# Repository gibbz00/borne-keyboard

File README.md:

# Borne V1 Keyboard

V2 interest check is now live: https://www.reddit.com/r/mechmarket/comments/10xzn65/ic_borne_v2_a_slim_wireless_and_split_keyboard/

Source files for the Borne Keyboard; a wireless, split, 36-key, orthogonal keyboard with a comparatively large battery capacity that should last over two months.
Also of low profile at a max height of about 17 mm (0.67 in).
Ready-made ZMK and Adafruit nrf52 bootloader binaries are placed in the `firmware/builds` directory.

Currently rocking this keyboard layout: http://www.keyboard-layout-editor.com/#/gists/0e81bf405ebbc268280f0506f7d0e771

**PLEASE NOTE THAT V1 IS A WORKING PROOF OF CONCEPT. Don't copy this project mindlessly and expect everything to work out of the box. I have notes containing over 500 points of improvements or cautions when working on this project, many of which to be added as repo issues in the near future.**

Kicad 6 and its component libraries are required to properly explore the majority of electronic design files. 

https://www.kicad.org/libraries/download/

Arch users simply install `kicad-library` and `kicad-library-3d-nightly` from the official repository.

# Customizing the keymap with ZMK

Necessary ZMK know-how can be found in its official documentation or in its welcoming community discord server: 

https://zmk.dev/docs

https://zmk.dev/community/discord/invite

## Building with GitHub Actions

Allows for keymap customizations to be done without going through the hassle of installing the respective toolchains. It works by automating firmware builds on a cloud server upon repository changes.

#### Repo setup (only once)
Log in/sign up to a personal GitHub account.
Fork https://github.com/gibbz00/borne-zmk-config
#### Keymap updates
Edit `config/borne.keymap`.
Commit and push changes to your personal repo.
#### Retrieving firmware images
In the browser; navigate to "Actions".
Select the latest workflow run.
A "firmware" artifact should appear if all went well, clicking on it should start a zip download, unzip it once completed.
#### Flashing the keyboard
Only the left shield/half/side needs to be built to update the keymap.
Connect the half over USB, put it in bootloader mode (double press reset), and make sure the device storage is mounted. 
Last step is to copy over the `borne_left-borne-zmk.uf2` file to the new USB storage device and wait until the blue LED stops blinking rapidly.

## Local builds and flashing

### Preparations

The following dependencies are required to build ZMK:
* zephyr-sdk 
* python-jsonschema
* remarshal

And for the Adafruit nRF52 bootloader:
* arm-none-eabi-gcc
* python-intelhex

For Arch Linux based distributions: All packages exist in the same name on AUR, e.g:
```
yay -S --needed python-intelhex arm-none-eabi-gcc zephyr-sdk python-jsonschema remarshal 
```

Bootloader and ZMK exist as submodules in this repository. (Not yet merged upstream.)
```
git clone URL && git submodule update
```

All firmware files unique to this keyboard are found in:
```
firmware/Adafruit_nRF52_Bootloader/src/boards/borne_keyboard/
firmware/zmk/app/boards/arm/borne-keyboard/
firmware/zmk/app/boards/shields/borne-keyboard/
```

Those only interested in updating the keymap need not look any further than:
```
firmware/zmk/app/boards/shields/borne-keyboard/borne.keymap
```

### Building ZMK

Only the left shield/half/side needs to be built to update the keymap:
```
# in the firmware/zmk/app directory
west build -d build/left --pristine --board borne -- -DSHIELD=borne_left
```
### Flashing ZMK
Connect the half over USB, put it in bootloader mode (double press reset), and make sure the device storage is mounted. Then:
```
# still in the firmware/zmk/app directory
cp build/left/zephyr/zmk.uf2 path_to_borne_mass_storage/CURRENT.uf2
```

If necessary, change the occurrences of "left" to "right" to build the other half. 

### Adafruit nrf52 bootloader

Multiple ways of building and then flashing the boards over UART is explained in Joric's diligent write-up: https://github.com/joric/nrfmicro/wiki/Bootloader

I only got flashing with OpenOCD on the Raspberry Pi 4 to work.
The hardware specific `openocd.cfg` is found in the `firmware` directory.
Additional resources on how to flash the nrf5240 with OpenOCD and a Raspberry Pi 4 are found at: https://www.rototron.info/circuitpython-nrf52840-dongle-openocd-pi-tutorial/

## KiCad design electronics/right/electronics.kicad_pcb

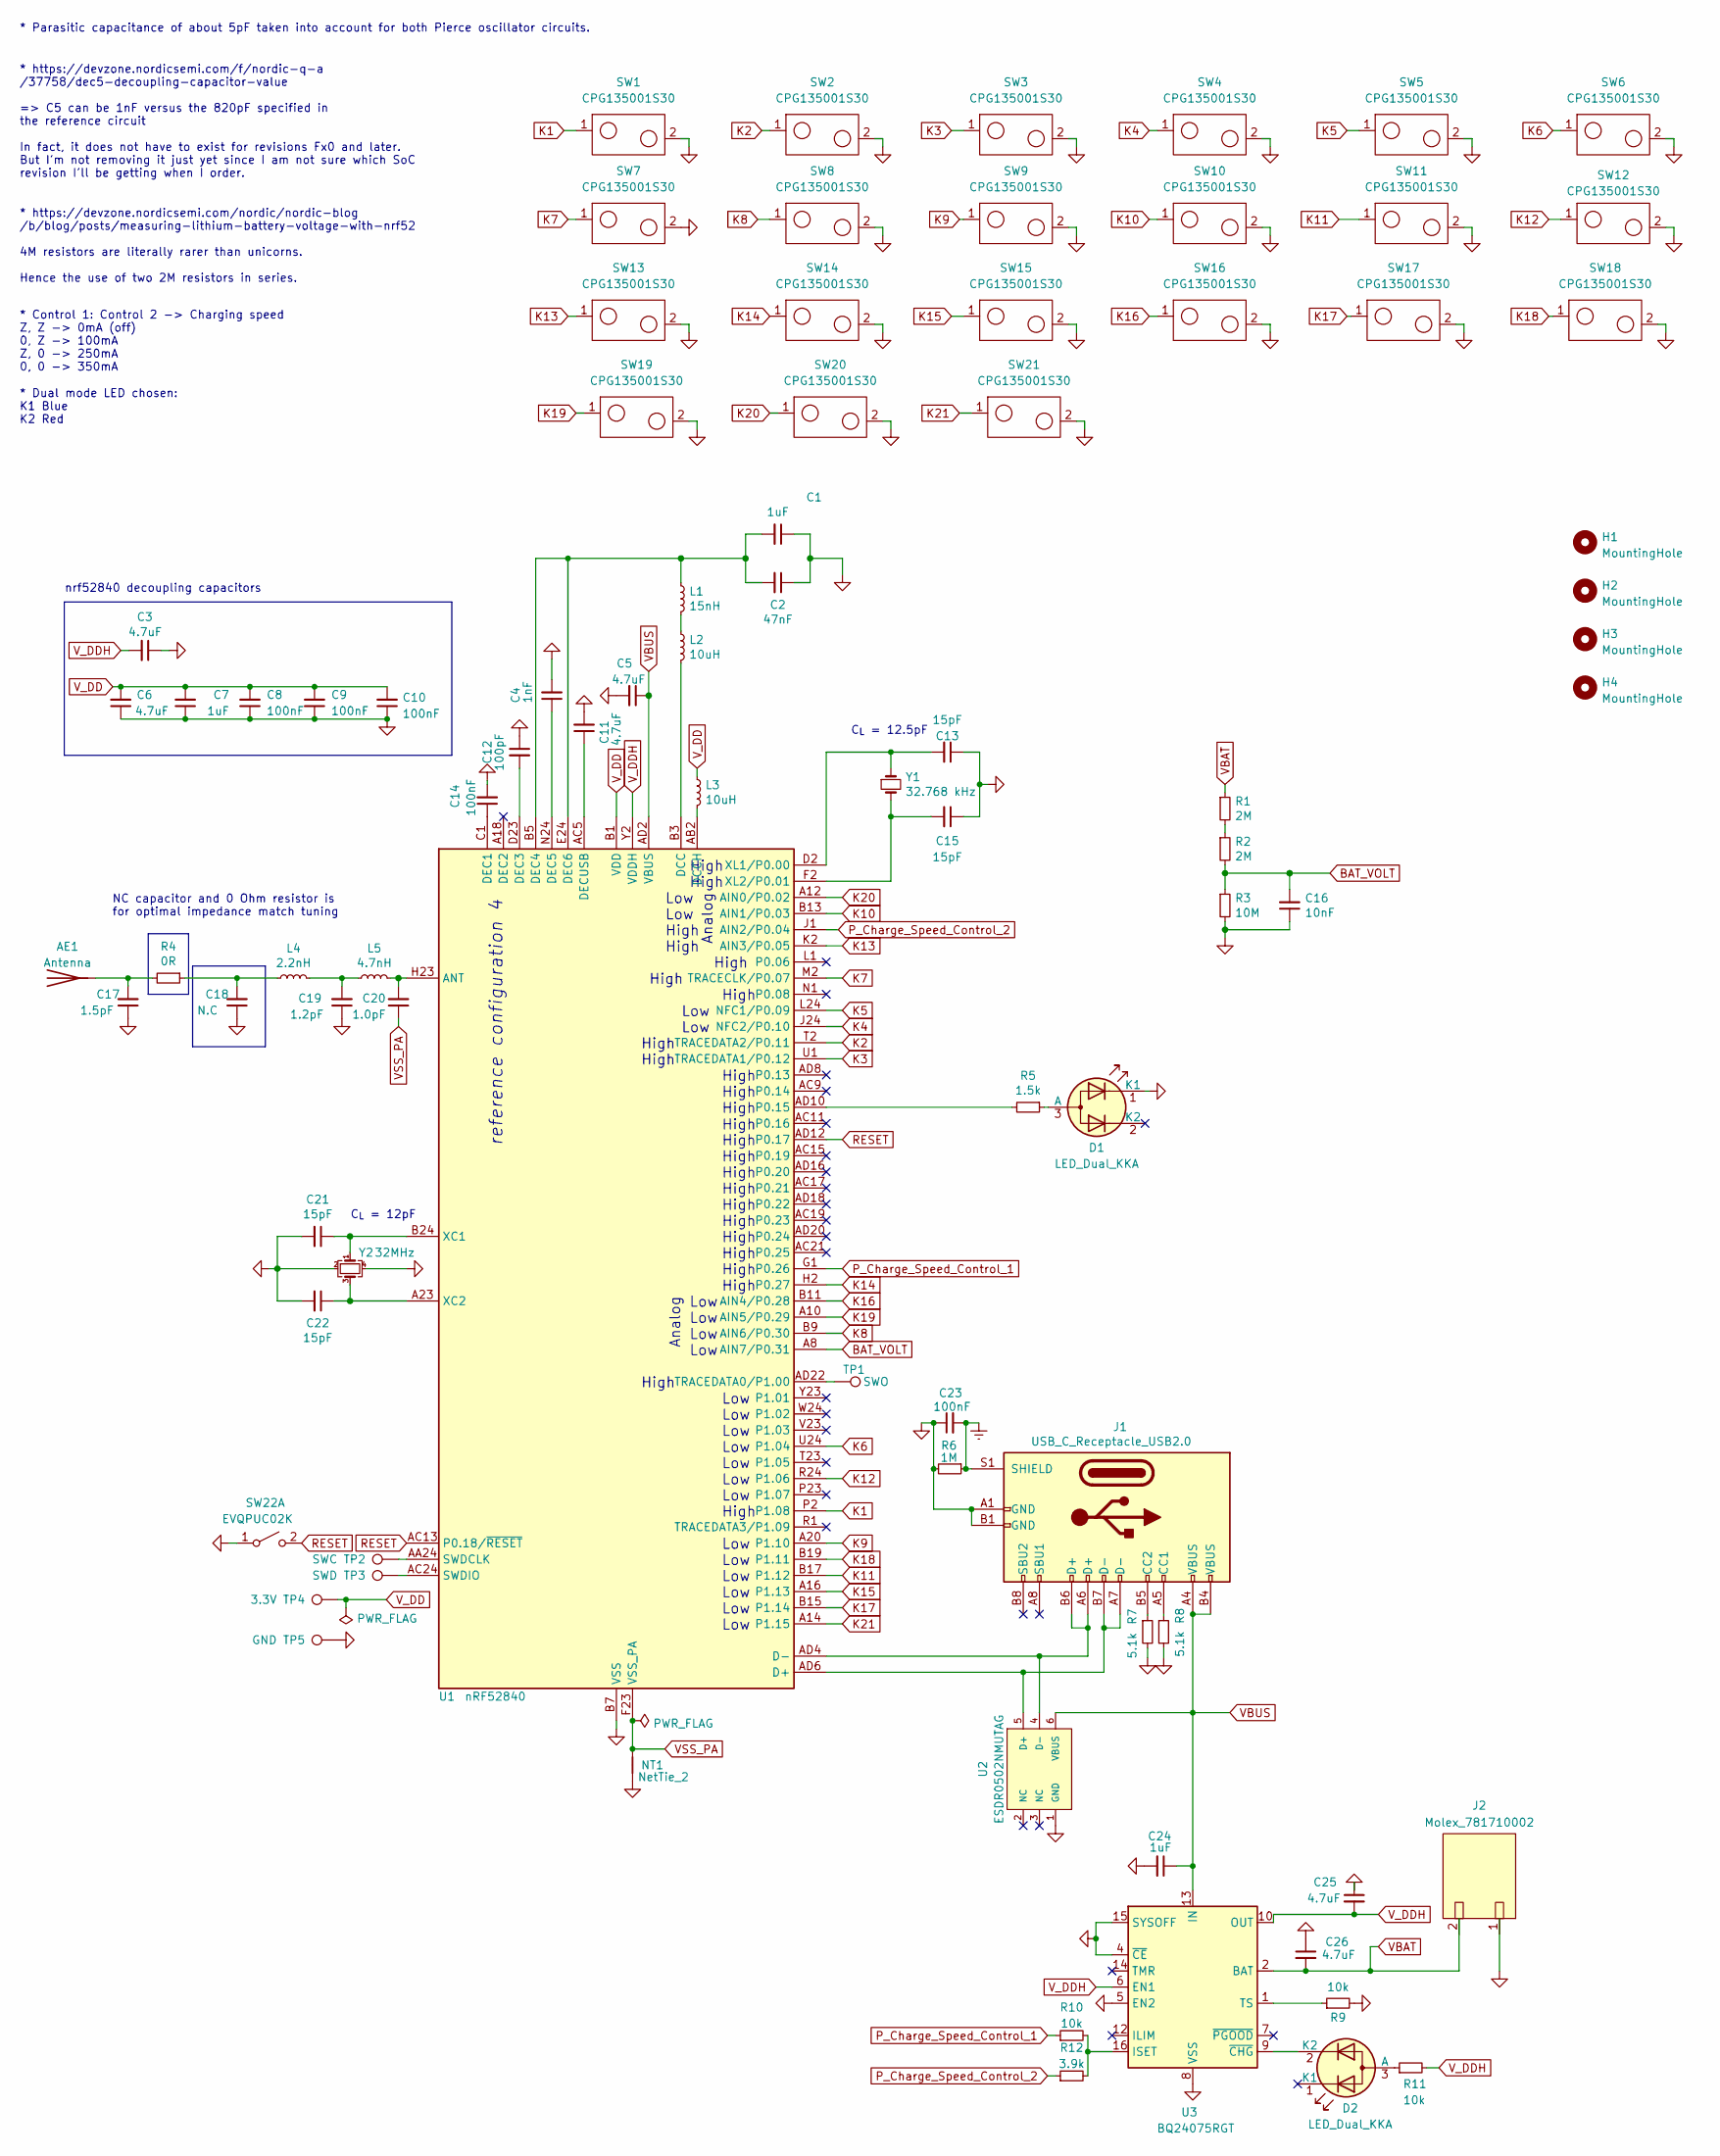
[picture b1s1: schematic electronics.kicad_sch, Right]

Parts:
AE1: Antenna; 2.4GHz-meander-antenna-right
C1, C7, C24: 1uF; C_0402_1005Metric; Manufacturer Part CL05A105KO5NNNC; LCSC Part C52923
C2: 47nF; C_0402_1005Metric; Manufacturer Part CL05B473KO5NNNC; LCSC Part C307434
C3, C5, C6, C11, C25, C26: 4.7uF; C_0402_1005Metric; Manufacturer Part CL05A475KP5NRNC; LCSC Part C368809
C4: 1nF; C_0402_1005Metric; Manufacturer Part CL05B104KA5NNNC; LCSC Part C1525
C8, C9, C10, C14: 100nF; C_0402_1005Metric; Manufacturer Part CL05B104KA5NNNC; LCSC Part C1525
C12: 100pF; C_0402_1005Metric; Manufacturer Part CL05C101JB5NNNC; LCSC Part C26409
C13, C15, C21, C22: 15pF; C_0402_1005Metric; Manufacturer Part CL05C150JB51PNC; LCSC Part C307341
C16: 10nF; C_0402_1005Metric; Manufacturer Part CL05B103KB5NNNC; LCSC Part C15195
C17: 1.5pF; C_0402_1005Metric; Manufacturer Part CL05C1R5CB5NNNC; LCSC Part C170150
C18: N.C; C_0402_1005Metric; Manufacturer Part CL05C010CB5NNNC; LCSC Part C371977
C19: 1.2pF; C_0402_1005Metric; Manufacturer Part CL05C010CB5NNNC; LCSC Part C371977
C20: 1.0pF; C_0402_1005Metric; Manufacturer Part CL05C010CB5NNNC; LCSC Part C371977
C23: 100nF; C_0402_1005Metric; Manufacturer Part CL05A475KP5NRNC; LCSC Part C368809
D1, D2: LED_Dual_KKA; LED-ARRAY-SMD_3P-L3.0-W2.0-L-FD; Manufacturer Part 12-22/BHR6C-A01/2C; LCSC Part C605447
H1, H2, H3, H4: MountingHole; screw-hole
J1: USB_C_Receptacle_USB2.0; USB-C-SMD_TYPE-C-31-M-13A-1; Manufacturer Part GT-USB-9014C; LCSC Part C2988367
J2: Molex_781710002; Molex_Pico-EZmate_78171-0002_1x02-1MP_P1.20mm_Vertical; Manufacturer Part 781710002; LCSC Part C505023
L1: 15nH; L_0402_1005Metric; Manufacturer Part MLG1005S15NJT000; LCSC Part C76763
L2, L3: 10uH; L_0603_1608Metric; Manufacturer Part MLF1608E100KTD00; LCSC Part C76732
L4: 2.2nH; L_0402_1005Metric; Manufacturer Part MLG1005S3N9BT000; LCSC Part C76775
L5: 4.7nH; L_0402_1005Metric; Manufacturer Part MLG1005S3N9BT000; LCSC Part C76775
NT1: NetTie_2; net-tie-2-tiny
R1, R2: 2M; R_0402_1005Metric; Manufacturer Part RC0402FR-072ML; LCSC Part C138014
R3: 10M; R_0402_1005Metric; Manufacturer Part RC0402FR-0710ML; LCSC Part C138067
R4: 0R; R_0402_1005Metric; Manufacturer Part RC0402FR-070RL; LCSC Part C106231
R5: 1.5k; R_0402_1005Metric; Manufacturer Part RC0402FR-071K5L; JLC Part C114759
R6: 1M; R_0402_1005Metric; Manufacturer Part RC0402FR-0710KL; LCSC Part C60490
R7, R8: 5.1k; R_0402_1005Metric; Manufacturer Part RC0402FR-0710KL; LCSC Part C60490
R9, R10, R11: 10k; R_0402_1005Metric; Manufacturer Part RC0402FR-0710KL; LCSC Part C60490
R12: 3.9k; R_0402_1005Metric; Manufacturer Part RC0402FR-073K9L; LCSC Part C131467
SW1, SW2, SW3, SW4, SW5, SW6, SW7, SW8, SW9, SW10, SW11, SW12, SW13, SW14, SW15, SW16, SW17, SW18, SW19, SW20, SW21: CPG135001S30; Kailh_socket_PG1350; Manufacturer Part CPG135001S30; JLC Part C5333465
SW22: EVQPUC02K; Panasonic_EVQPUL_EVQPUC; Manufacturer Part EVQPUC02K; JLC Part C79174
TP1: SWO; TestPoint_THTPad_1.5x1.5mm_Drill0.7mm
TP2: SWC; TestPoint_THTPad_1.5x1.5mm_Drill0.7mm
TP3: SWD; TestPoint_THTPad_1.5x1.5mm_Drill0.7mm
TP4: 3.3V; TestPoint_THTPad_1.5x1.5mm_Drill0.7mm
TP5: GND; TestPoint_THTPad_1.5x1.5mm_Drill0.7mm
U1: nRF52840; Nordic_AQFN-73-1EP_7x7mm_P0.5mm; Manufacturer Part NRF52840-QIAA-R; LCSC Part C1851953
U2: ESDR0502NMUTAG; Manufacturer Part ESDR0502NMUTBG; LCSC Part C327480
U3: BQ24075RGT; VQFN-16-1EP_3x3mm_P0.5mm_EP1.6x1.6mm; Manufacturer Part BQ24075RGTR; JLC Part C15464
Y1: 32.768 kHz; Crystal_SMD_2012-2Pin_2.0x1.2mm; Manufacturer Part SC20S-12.5PF20PPM; LCSC Part C97607
Y2: 32MHz; Crystal_SMD_2016-4Pin_2.0x1.6mm; Manufacturer Part Q22FA1280001800; LCSC Part C255896

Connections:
BAT_VOLT: C16.2, R2.2, R3.1, U1.A8 (AIN7/P0.31)
K1: SW1.1, U1.P2 (P1.08)
K2: SW2.1, U1.T2 (TRACEDATA2/P0.11)
K3: SW3.1, U1.U1 (TRACEDATA1/P0.12)
K4: SW4.1, U1.J24 (NFC2/P0.10)
K5: SW5.1, U1.L24 (NFC1/P0.09)
K6: SW6.1, U1.U24 (P1.04)
K7: SW7.1, U1.M2 (TRACECLK/P0.07)
K8: SW8.1, U1.B9 (AIN6/P0.30)
K9: SW9.1, U1.A20 (P1.10)
K10: SW10.1, U1.B13 (AIN1/P0.03)
K11: SW11.1, U1.B17 (P1.12)
K12: SW12.1, U1.R24 (P1.06)
K13: SW13.1, U1.K2 (AIN3/P0.05)
K14: SW14.1, U1.H2 (P0.27)
K15: SW15.1, U1.A16 (P1.13)
K16: SW16.1, U1.B11 (AIN4/P0.28)
K17: SW17.1, U1.B15 (P1.14)
K18: SW18.1, U1.B19 (P1.11)
K19: SW19.1, U1.A10 (AIN5/P0.29)
K20: SW20.1, U1.A12 (AIN0/P0.02)
K21: SW21.1, U1.A14 (P1.15)
unnamed: AE1.1 (A), C17.2, R4.2
unnamed: C18.2, L4.2, R4.1
unnamed: C19.2, L4.1, L5.1
unnamed: D1.3 (A), R5.1
unnamed: D2.3 (A), R11.1
unnamed: D2.2 (K2), U3.9 (~CHG)
unnamed: J1.A5 (CC1), R8.1
unnamed: J1.B5 (CC2), R7.1
unnamed: L1.2, L2.1
unnamed: R1.2, R2.1
unnamed: C20.2, L5.2, U1.H23 (ANT)
unnamed: J1.A7 (D-), J1.B7 (D-), U1.AD6 (D+), U2.5 (D+)
unnamed: J1.A6 (D+), J1.B6 (D+), U1.AD4 (D-), U2.4 (D-)
unnamed: L2.2, U1.B3 (DCC)
unnamed: L3.2, U1.AB2 (DCCH)
unnamed: C14.1, U1.C1 (DEC1)
unnamed: C12.2, U1.D23 (DEC3)
unnamed: C1.2, C2.2, L1.1, U1.B5 (DEC4), U1.E24 (DEC6)
unnamed: C4.1, U1.N24 (DEC5)
unnamed: C11.1, U1.AC5 (DECUSB)
unnamed: R5.2, U1.AD10 (P0.15)
unnamed: TP2.1, U1.AA24 (SWDCLK)
unnamed: TP3.1, U1.AC24 (SWDIO)
unnamed: TP1.1, U1.AD22 (TRACEDATA0/P1.00)
unnamed: C21.1, U1.B24 (XC1), Y2.1
unnamed: C22.1, U1.A23 (XC2), Y2.3
unnamed: C13.2, U1.D2 (XL1/P0.00), Y1.1
unnamed: C15.2, U1.F2 (XL2/P0.01), Y1.2
unnamed: R10.2, R12.2, U3.16 (ISET)
unnamed: R9.1, U3.1 (TS)
P_Charge_Speed_Control_1: R10.1, U1.G1 (P0.26)
P_Charge_Speed_Control_2: R12.1, U1.J1 (AIN2/P0.04)
RESET: SW22.2 (B), U1.AC13 (P0.18/~RESET), U1.AD12 (P0.17)
VBAT: C26.2, J2.2, R1.1, U3.2 (BAT), U3.3 (BAT)
VBUS: C5.1, C24.1, J1.A4 (VBUS), J1.B4 (VBUS), U1.AD2 (VBUS), U2.6 (VBUS), U3.13 (IN)
VSS_PA: C20.1, NT1.1, U1.F23 (VSS_PA)
V_DD: C6.2, C7.2, C8.2, C9.2, C10.2, L3.1, TP4.1, U1.A22 (VDD), U1.AD14 (VDD), U1.AD23 (VDD), U1.B1 (VDD), U1.W1 (VDD)
V_DDH: C3.2, C25.2, R11.2, U1.Y2 (VDDH), U3.6 (EN1), U3.10 (OUT), U3.11 (OUT)

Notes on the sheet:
High
Low
C_{L} = 12pF
* Dual mode LED chosen: K1 Blue K2 Red
* https://devzone.nordicsemi.com/nordic/nordic-blog /b/blog/posts/measuring-lithium-battery-voltage-with-nrf52 4M resistors are literally rarer than unicorns. Hence the use of two 2M resistors in series.
nrf52840 decoupling capacitors
* Parasitic capacitance of about 5pF taken into account for both Pierce oscillator circuits.
reference configuration 4
C_{L} = 12.5pF
* https://devzone.nordicsemi.com/f/nordic-q-a /37758/dec5-decoupling-capacitor-value => C5 can be 1nF versus the 820pF specified in the reference circuit In fact, it does not have to exist for revisions Fx0 and later. But I'm not removing it just yet since I am not sure which SoC revision I'll be g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
* Control 1: Control 2 -> Charging speed Z, Z -> 0mA (off) 0, Z -> 100mA Z, 0 -> 250mA 0, 0 -> 350mA
Analog
NC capacitor and 0 Ohm resistor is for optimal impedance match tuning

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
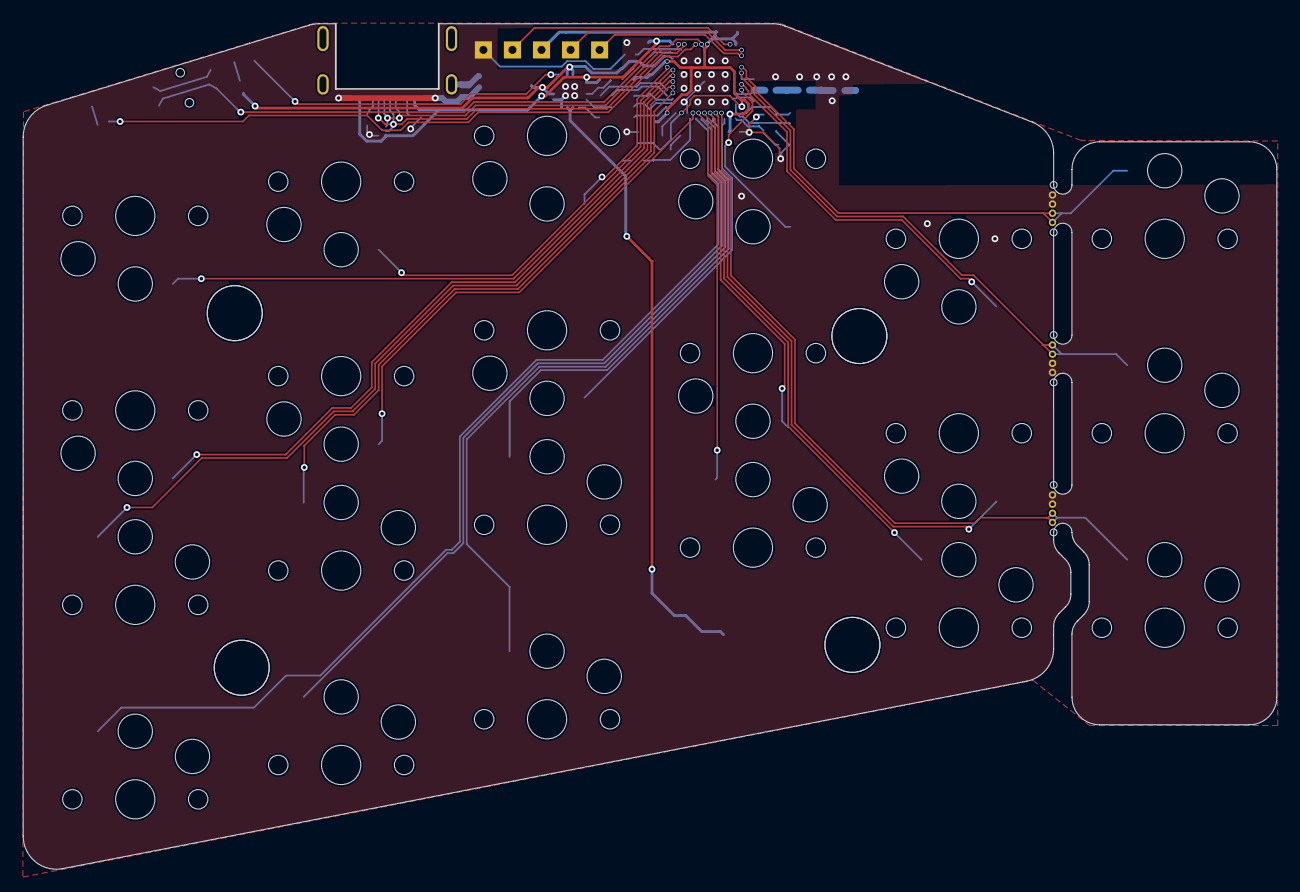
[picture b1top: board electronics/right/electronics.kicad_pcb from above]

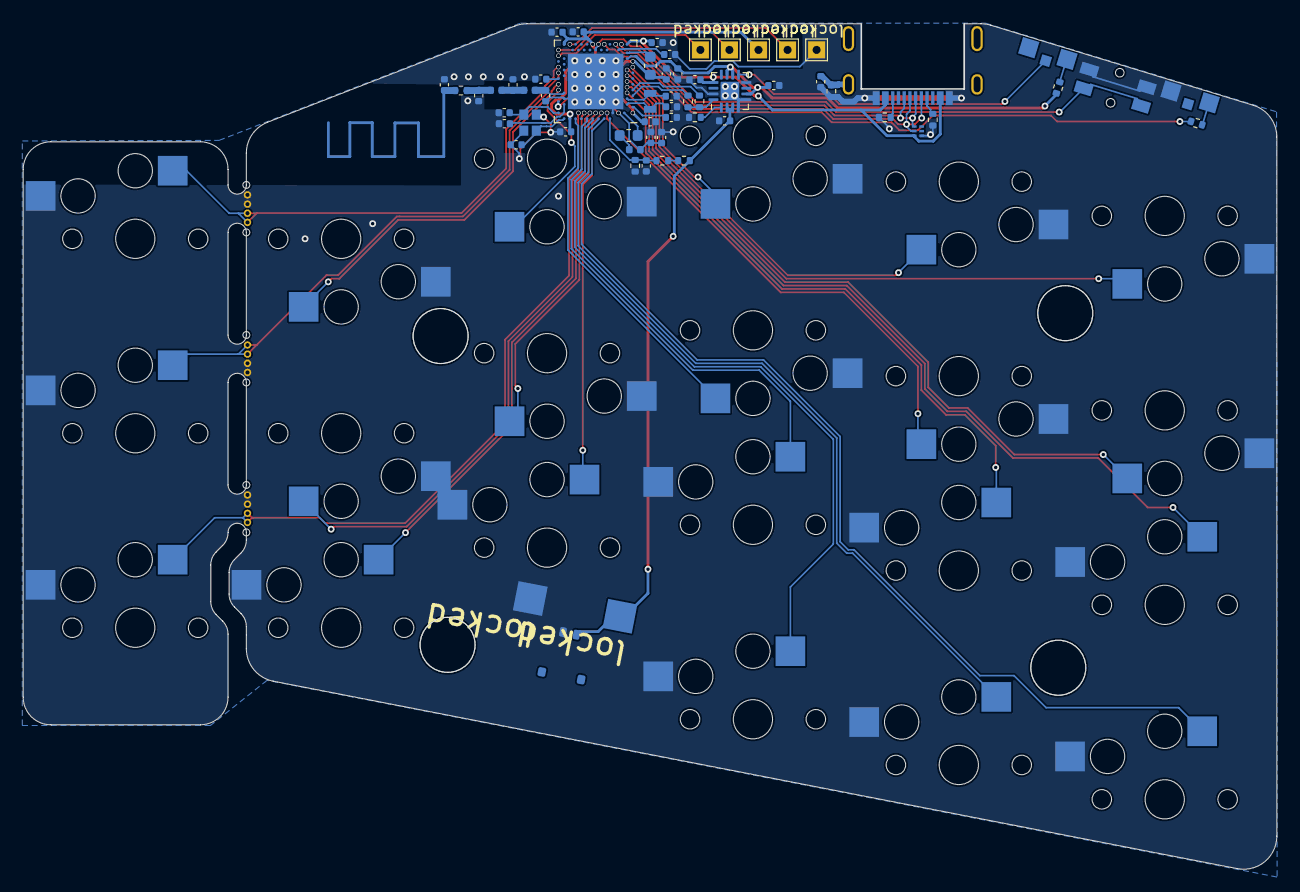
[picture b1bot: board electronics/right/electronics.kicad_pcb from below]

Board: 2 copper layers, 109.5 x 73.9 mm, 88 parts (81 on the bottom side), 62 nets.

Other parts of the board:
mouse-bite-5mm-slot, mouse-bite-5mm-slot#2, mouse-bite-5mm-slot#3: VAL**; pcb-way-single-mouse-bites-plated

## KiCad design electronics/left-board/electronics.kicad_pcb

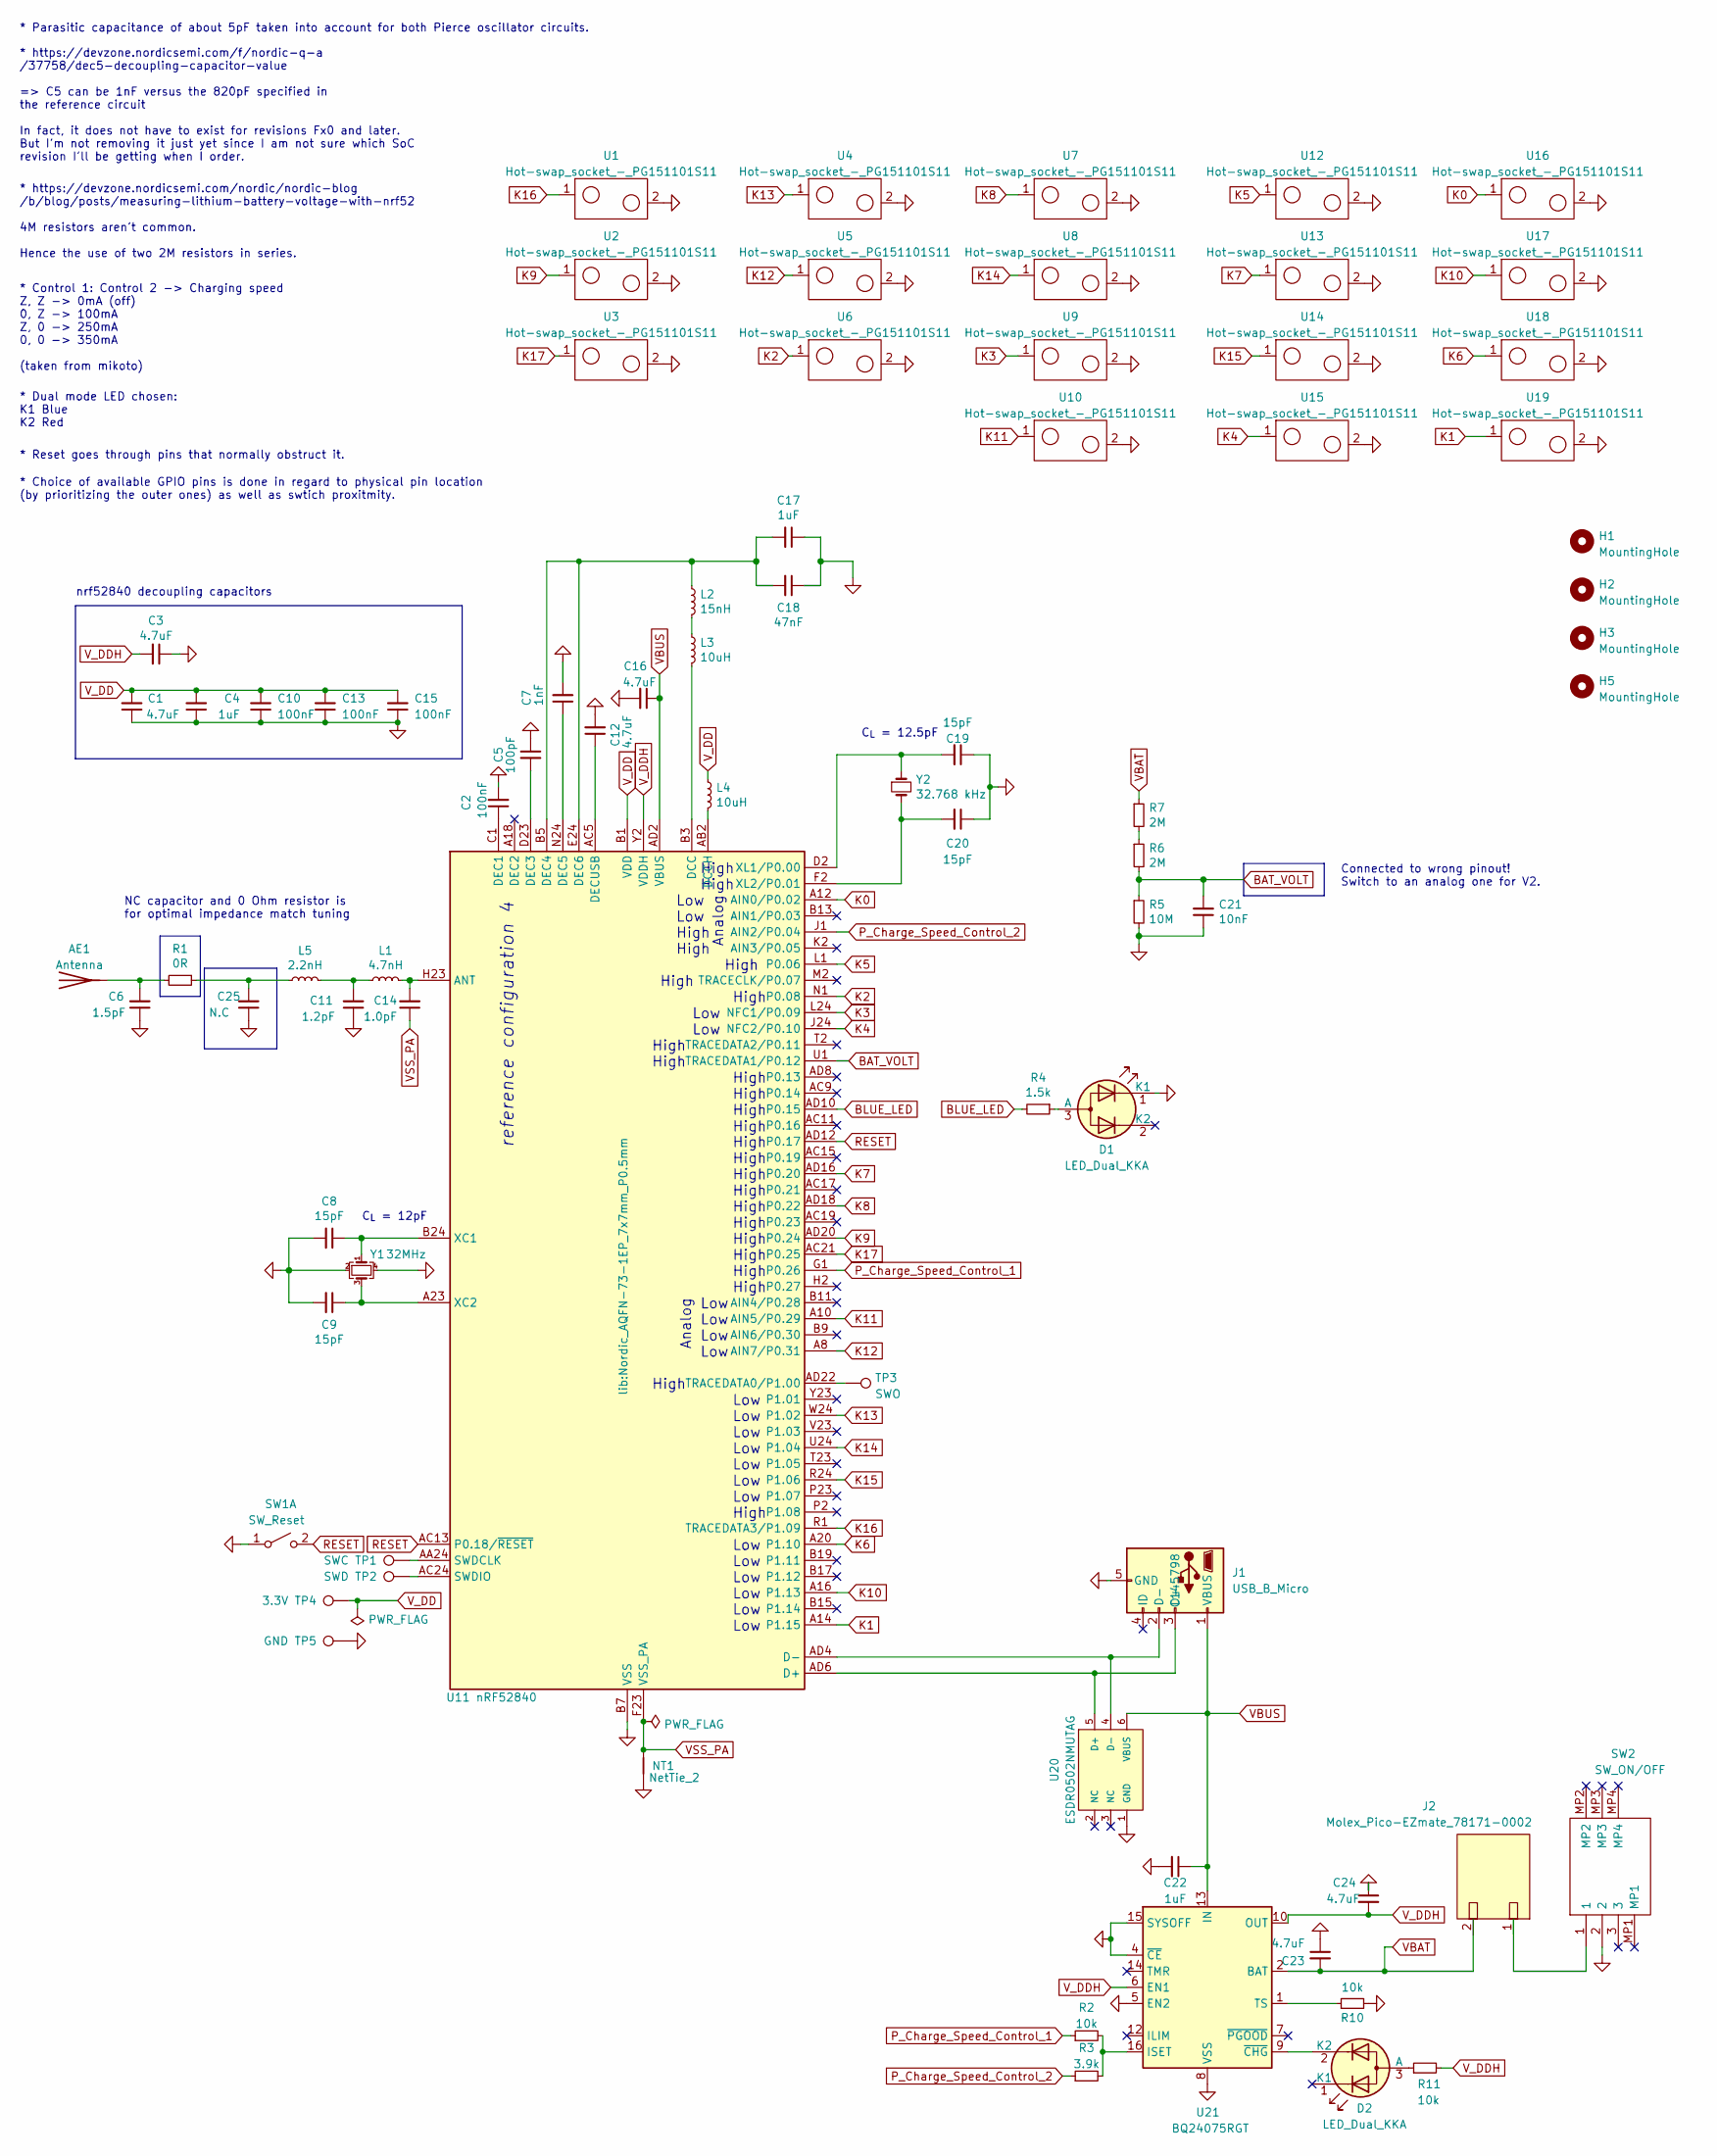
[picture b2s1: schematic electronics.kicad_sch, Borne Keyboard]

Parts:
AE1: Antenna; 2.4GHz-meander-antenna-left
C1, C3, C12, C16, C23, C24: 4.7uF; C_0402_1005Metric; Manufacturer Part CL05A475KP5NRNC; LCSC Part C368809
C2, C10, C13, C15: 100nF; C_0402_1005Metric; Manufacturer Part CL05B104KA5NNNC; LCSC Part C1525
C4, C17, C22: 1uF; C_0402_1005Metric; Manufacturer Part CL05A105KO5NNNC; LCSC Part C52923
C5: 100pF; C_0402_1005Metric; Manufacturer Part CL05C101JB5NNNC; LCSC Part C26409
C6: 1.5pF; C_0402_1005Metric; Manufacturer Part CL05C1R5CB5NNNC; LCSC Part C170150
C7: 1nF; C_0402_1005Metric; Manufacturer Part CL05B104KA5NNNC; LCSC Part C1525
C8, C9, C19, C20: 15pF; C_0402_1005Metric; Manufacturer Part CL05C150JB51PNC; LCSC Part C307341
C11: 1.2pF; C_0402_1005Metric; Manufacturer Part CL05C010CB5NNNC; LCSC Part C371977
C14: 1.0pF; C_0402_1005Metric; Manufacturer Part CL05C010CB5NNNC; LCSC Part C371977
C18: 47nF; C_0402_1005Metric; Manufacturer Part CL05B473KO5NNNC; LCSC Part C307434
C21: 10nF; C_0402_1005Metric; Manufacturer Part CL05B103KB5NNNC; LCSC Part C15195
C25: N.C; C_0402_1005Metric; Manufacturer Part CL05C010CB5NNNC; LCSC Part C371977
D1, D2: LED_Dual_KKA; LED-ARRAY-SMD_3P-L3.0-W2.0-L-FD; Manufacturer Part 12-22/BHR6C-A01/2C; LCSC Part C605447
H1, H2, H3, H5: MountingHole; screw-hole
J1: USB_B_Micro; MICRO-USB-SMD_U-C-M5DD-W-1; Manufacturer Part U-C-M5DD-W-1; LCSC Part C145798
J2: Molex_Pico-EZmate_78171-0002; Molex_Pico-EZmate_78171-0002_1x02-1MP_P1.20mm_Vertical; Manufacturer Part Molex_Pico-EZmate_78171-0002; LCSC Part C505023
L1: 4.7nH; L_0402_1005Metric; Manufacturer Part MLG1005S3N9BT000; LCSC Part C76775
L2: 15nH; L_0402_1005Metric; Manufacturer Part MLG1005S15NJT000; LCSC Part C76763
L3, L4: 10uH; L_0603_1608Metric; Manufacturer Part MLF1608E100KTD00; LCSC Part C76732
L5: 2.2nH; L_0402_1005Metric; Manufacturer Part MLG1005S3N9BT000; LCSC Part C76775
NT1: NetTie_2; net-tie-2-tiny
R1: 0R; R_0402_1005Metric; Manufacturer Part RC0402FR-070RL; LCSC Part C106231
R2, R10, R11: 10k; R_0402_1005Metric; Manufacturer Part RC0402FR-0710KL; LCSC Part C60490
R3: 3.9k; R_0402_1005Metric; Manufacturer Part RC0402FR-073K9L; LCSC Part C131467
R4: 1.5k; R_0402_1005Metric; Manufacturer Part RC0402FR-071K5L; JLC Part C114759
R5: 10M; R_0402_1005Metric; Manufacturer Part RC0402FR-0710ML; LCSC Part C138067
R6, R7: 2M; R_0402_1005Metric; Manufacturer Part RC0402FR-072ML; LCSC Part C138014
SW1: SW_Reset; Panasonic_EVQPUL_EVQPUC; Manufacturer Part EVQPUC02K; JLC Part C79174
SW2: SW_ON/OFF; SK3296S01L3; Manufacturer Part SK-3296S-01-L3; LCSC Part C319019
TP1: SWC; TestPoint_THTPad_2.5x2.5mm_Drill1.2mm
TP2: SWD; TestPoint_THTPad_2.5x2.5mm_Drill1.2mm
TP3: SWO; TestPoint_THTPad_2.5x2.5mm_Drill1.2mm
TP4: 3.3V; TestPoint_THTPad_2.5x2.5mm_Drill1.2mm
TP5: GND; TestPoint_THTPad_2.5x2.5mm_Drill1.2mm
U1, U2, U3, U4, U5, U6, U7, U8, U9, U10, U12, U13, U14, U15, U16, U17, U18, U19: Hot-swap_socket_-_PG151101S11; Kailh_socket_PG1350; Manufacturer Part CPG151101S11; JLC Part C2803348
U11: nRF52840; Nordic_AQFN-73-1EP_7x7mm_P0.5mm; Manufacturer Part NRF52840-QIAA-R; LCSC Part C1851953
U20: ESDR0502NMUTAG; Manufacturer Part ESDR0502NMUTBG; LCSC Part C327480
U21: BQ24075RGT; VQFN-16-1EP_3x3mm_P0.5mm_EP1.6x1.6mm; Manufacturer Part BQ24075RGTR; JLC Part C15464
Y1: 32MHz; Crystal_SMD_2016-4Pin_2.0x1.6mm; Manufacturer Part Q22FA1280001800; LCSC Part C255896
Y2: 32.768 kHz; Crystal_SMD_2012-2Pin_2.0x1.2mm; Manufacturer Part SC20S-12.5PF20PPM; LCSC Part C97607

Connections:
BAT_VOLT: C21.2, R5.1, R6.2, U11.U1 (TRACEDATA1/P0.12)
BLUE_LED: R4.2, U11.AD10 (P0.15)
GND: C1.1, C2.2, C3.1, C4.1, C5.1, C6.1, C7.2, C8.2, C9.2, C10.1, C11.1, C12.2, C13.1, C15.1, C16.2, C17.1, C18.1, C19.1, C20.1, C21.1, C22.2, C23.1, C24.1, C25.1, D1.1 (K1), J1.5 (GND), NT1.2, R5.2, R10.2, SW1.1 (A), SW2.2, TP5.1, U1.2, U2.2, U3.2, U4.2, U5.2, U6.2, U7.2, U8.2, U9.2, U10.2, U11.B7 (VSS), U11.EP (VSS), U12.2, U13.2, U14.2, U15.2, U16.2, U17.2, U18.2, U19.2, U20.1 (GND), U21.4 (~CE), U21.5 (EN2), U21.8 (VSS), U21.15 (SYSOFF), U21.17 (VSS), Y1.2, Y1.4
K0: U11.A12 (AIN0/P0.02), U16.1
K1: U11.A14 (P1.15), U19.1
K2: U6.1, U11.N1 (P0.08)
K3: U9.1, U11.L24 (NFC1/P0.09)
K4: U11.J24 (NFC2/P0.10), U15.1
K5: U11.L1 (P0.06), U12.1
K6: U11.A20 (P1.10), U18.1
K7: U11.AD16 (P0.20), U13.1
K8: U7.1, U11.AD18 (P0.22)
K9: U2.1, U11.AD20 (P0.24)
K10: U11.A16 (P1.13), U17.1
K11: U10.1, U11.A10 (AIN5/P0.29)
K12: U5.1, U11.A8 (AIN7/P0.31)
K13: U4.1, U11.W24 (P1.02)
K14: U8.1, U11.U24 (P1.04)
K15: U11.R24 (P1.06), U14.1
K16: U1.1, U11.R1 (TRACEDATA3/P1.09)
K17: U3.1, U11.AC21 (P0.25)
unnamed: AE1.1 (A), C6.2, R1.2
unnamed: C2.1, U11.C1 (DEC1)
unnamed: C5.2, U11.D23 (DEC3)
unnamed: C7.1, U11.N24 (DEC5)
unnamed: C8.1, U11.B24 (XC1), Y1.1
unnamed: C9.1, U11.A23 (XC2), Y1.3
unnamed: C11.2, L1.1, L5.1
unnamed: C12.1, U11.AC5 (DECUSB)
unnamed: C14.2, L1.2, U11.H23 (ANT)
unnamed: C17.2, C18.2, L2.1, U11.B5 (DEC4), U11.E24 (DEC6)
unnamed: C19.2, U11.D2 (XL1/P0.00), Y2.1
unnamed: C20.2, U11.F2 (XL2/P0.01), Y2.2
unnamed: C25.2, L5.2, R1.1
unnamed: D1.3 (A), R4.1
unnamed: D2.2 (K2), U21.9 (~CHG)
unnamed: D2.3 (A), R11.1
unnamed: J1.2 (D-), U11.AD4 (D-), U20.4 (D-)
unnamed: J1.3 (D+), U11.AD6 (D+), U20.5 (D+)
unnamed: J2.1, SW2.1
unnamed: L2.2, L3.1
unnamed: L3.2, U11.B3 (DCC)
unnamed: L4.2, U11.AB2 (DCCH)
unnamed: R2.2, R3.2, U21.16 (ISET)
unnamed: R6.1, R7.2
unnamed: R10.1, U21.1 (TS)
unnamed: TP1.1, U11.AA24 (SWDCLK)
unnamed: TP2.1, U11.AC24 (SWDIO)
unnamed: TP3.1, U11.AD22 (TRACEDATA0/P1.00)
P_Charge_Speed_Control_1: R2.1, U11.G1 (P0.26)
P_Charge_Speed_Control_2: R3.1, U11.J1 (AIN2/P0.04)
RESET: SW1.2 (B), U11.AC13 (P0.18/~RESET), U11.AD12 (P0.17)
VBAT: C23.2, J2.2, R7.1, U21.2 (BAT), U21.3 (BAT)
VBUS: C16.1, C22.1, J1.1 (VBUS), U11.AD2 (VBUS), U20.6 (VBUS), U21.13 (IN)
VSS_PA: C14.1, NT1.1, U11.F23 (VSS_PA)
V_DD: C1.2, C4.2, C10.2, C13.2, C15.2, L4.1, TP4.1, U11.A22 (VDD), U11.AD14 (VDD), U11.AD23 (VDD), U11.B1 (VDD), U11.W1 (VDD)
V_DDH: C3.2, C24.2, R11.2, U11.Y2 (VDDH), U21.6 (EN1), U21.10 (OUT), U21.11 (OUT)

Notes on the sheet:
High
Low
nrf52840 decoupling capacitors
* Dual mode LED chosen: K1 Blue K2 Red
* Control 1: Control 2 -> Charging speed Z, Z -> 0mA (off) 0, Z -> 100mA Z, 0 -> 250mA 0, 0 -> 350mA (taken from mikoto)
* Reset goes through pins that normally obstruct it.
* https://devzone.nordicsemi.com/nordic/nordic-blog /b/blog/posts/measuring-lithium-battery-voltage-with-nrf52 4M resistors aren't common. Hence the use of two 2M resistors in series.
* Parasitic capacitance of about 5pF taken into account for both Pierce oscillator circuits.
NC capacitor and 0 Ohm resistor is for optimal impedance match tuning
Analog
C_{L} = 12.5pF
* Choice of available GPIO pins is done in regard to physical pin location (by prioritizing the outer ones) as well as swtich proxitmity.
C_{L} = 12pF
Connected to wrong pinout! Switch to an analog one for V2.
* https://devzone.nordicsemi.com/f/nordic-q-a /37758/dec5-decoupling-capacitor-value => C5 can be 1nF versus the 820pF specified in the reference circuit In fact, it does not have to exist for revisions Fx0 and later. But I'm not removing it just yet since I am not sure which SoC revision I'll be g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
reference configuration 4
